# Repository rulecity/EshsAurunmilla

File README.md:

# Esh's Aurunmilla
(Mostly) 1:1 clone of the arcade game PCB for the Funai game, Esh's Aurunmilla

# Introduction
Esh's Aurunmilla was laserdisc game conversion for the 1983 Funai game Interstellar.  It is notoriously campy/cheesy with pretty bad voice acting.  In short, the game is so bad that it's good.

I became fascinated with this game some years ago and desired to own one.  Unfortunately, the PCB and laserdisc are both exceedingly rare.  So instead of finding originals of these items, I created reproductions.  I created a mostly 1:1 clone of the game PCB which is what this repository consists of.  After selling 20 of these clones to collectors and exhausting commercial demand, I decided to open source the whole thing for preservation.  What you have in this repository are the results of my efforts.

# PCBs
I created the PCB with Kicad v5.  I have tested these files on Kicad v6 and they seem to work fine.
I made two smaller PCBs to replace the original PROMs used on these games, which are very obsolete.  The small PCBs use CPLDs to mimic the behavior of the PROMs.  Unfortunately, these CPLDs have themselves become obsolete (I chose them because they were 5V tolerant on the inputs).  But someone who knows what they are doing should be able to update these with a new CPLD/FPGA if they want to badly enough.

I said before that the PCB is a mostly 1:1 clone.  I did change the laserdisc I/O port because the one on the original PCB was hopelessly non-standard.  I also removed some diagnostic stuff that was near the CPU on the original PCB as I saw no benefit to retaining it.  Otherwise, this clone should be nearly identical to the original, trace for trace.

# VHDL
I've included the simple VHDL source code programs I wrote for the two CPLDs.  I built with Xilinx ISE 14.7 which, last I checked, can be obtained for free as a linux VM that runs fine under Windows in VirtualBox.

# Bill of Materials
These are the actual spreadsheets I used when ordering parts for these PCBs.

# Test ROM
A test ROM I wrote from scratch to test PCBs before I shipped them off to customers.  Should be pretty comprehensive.

# More info
See http://www.rulecity.com/esh/

# Support
If you need help building the VHDL code, programming the CPLDs, or having PCBs made from the KiCad files, I offer commercial support: https://www.daphne-emu.com:9443/mediawiki/index.php/CommercialSupport

--Matt Ownby

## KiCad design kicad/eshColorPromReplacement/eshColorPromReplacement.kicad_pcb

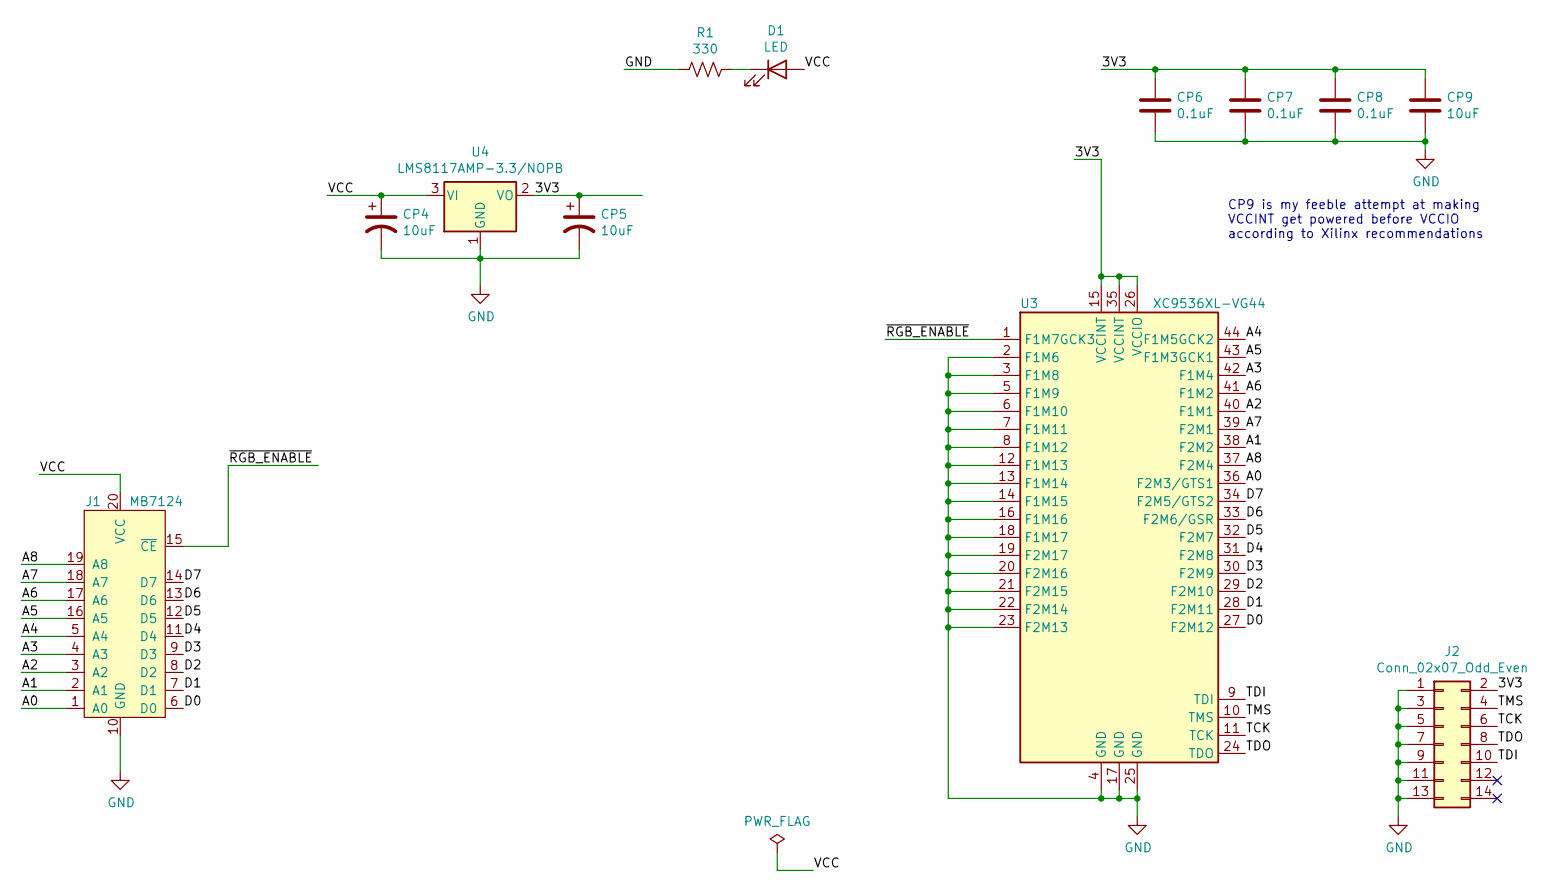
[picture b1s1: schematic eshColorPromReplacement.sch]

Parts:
CP4, CP5, CP9: 10uF; C_1206_3216Metric
CP6, CP7, CP8: 0.1uF; C_1206_3216Metric
D1: LED; LED_1206_3216Metric
J1: MB7124; DIP-20_W7.62mm_Socket
J2: Conn_02x07_Odd_Even; PinHeader_2x07_P2.54mm_Vertical
R1: 330; R_1206_3216Metric
U3: XC9536XL-VG44; TQFP-44_10x10mm_P0.8mm
U4: LMS8117AMP-3.3/NOPB; SOT-223-3_TabPin2

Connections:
/3V3: CP5.1, CP6.1, CP7.1, CP8.1, CP9.1, J2.2, U3.15 (VCCINT), U3.26 (VCCIO), U3.35 (VCCINT), U4.2 (VO)
/A0: J1.1 (A0), U3.36 (F2M3/GTS1)
/A1: J1.2 (A1), U3.38 (F2M2)
/A2: J1.3 (A2), U3.40 (F1M1)
/A3: J1.4 (A3), U3.42 (F1M4)
/A4: J1.5 (A4), U3.44 (F1M5GCK2)
/A5: J1.16 (A5), U3.43 (F1M3GCK1)
/A6: J1.17 (A6), U3.41 (F1M2)
/A7: J1.18 (A7), U3.39 (F2M1)
/A8: J1.19 (A8), U3.37 (F2M4)
/D0: J1.6 (D0), U3.27 (F2M12)
/D1: J1.7 (D1), U3.28 (F2M11)
/D2: J1.8 (D2), U3.29 (F2M10)
/D3: J1.9 (D3), U3.30 (F2M9)
/D4: J1.11 (D4), U3.31 (F2M8)
/D5: J1.12 (D5), U3.32 (F2M7)
/D6: J1.13 (D6), U3.33 (F2M6/GSR)
/D7: J1.14 (D7), U3.34 (F2M5/GTS2)
/TCK: J2.6, U3.11 (TCK)
/TDI: J2.10, U3.9 (TDI)
/TDO: J2.8, U3.24 (TDO)
/TMS: J2.4, U3.10 (TMS)
/VCC: CP4.1, D1.2 (A), J1.20 (VCC), U4.3 (VI)
/~RGB_ENABLE: J1.15 (~CE), U3.1 (F1M7GCK3)
GND: CP4.2, CP5.2, CP6.2, CP7.2, CP8.2, CP9.2, J1.10 (GND), J2.1, J2.3, J2.5, J2.7, J2.9, J2.11, J2.13, R1.2, U3.2 (F1M6), U3.3 (F1M8), U3.4 (GND), U3.5 (F1M9), U3.6 (F1M10), U3.7 (F1M11), U3.8 (F1M12), U3.12 (F1M13), U3.13 (F1M14), U3.14 (F1M15), U3.16 (F1M16), U3.17 (GND), U3.18 (F1M17), U3.19 (F2M17), U3.20 (F2M16), U3.21 (F2M15), U3.22 (F2M14), U3.23 (F2M13), U3.25 (GND), U4.1 (GND)
unnamed: D1.1 (K), R1.1

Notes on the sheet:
CP9 is my feeble attempt at making VCCINT get powered before VCCIO according to Xilinx recommendations

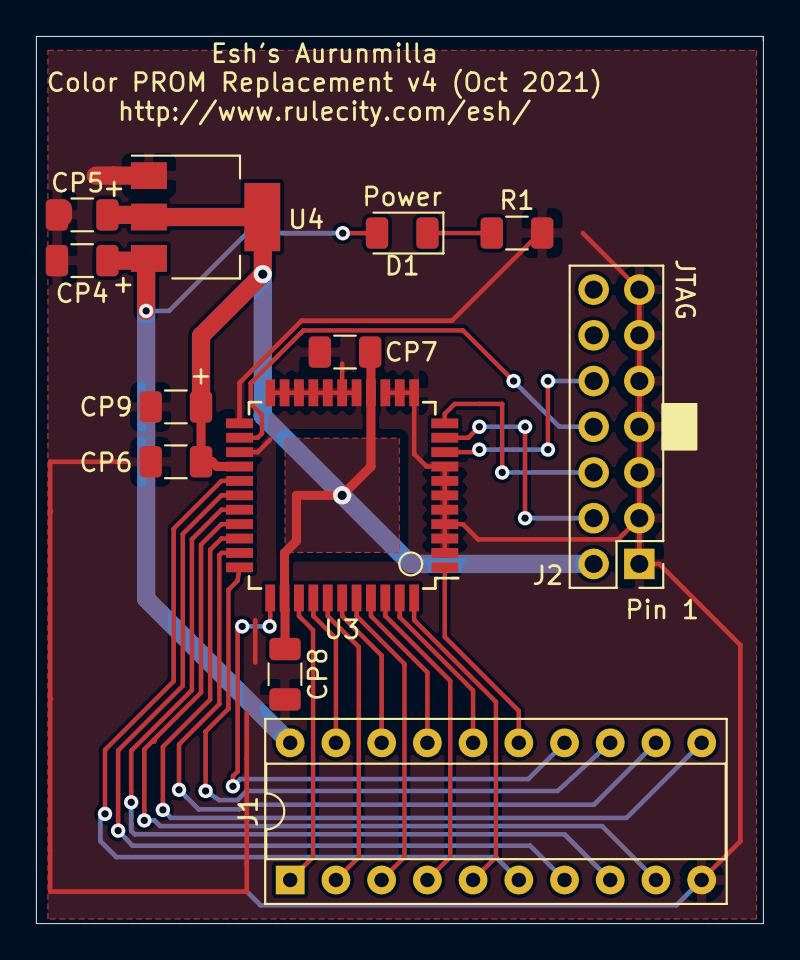
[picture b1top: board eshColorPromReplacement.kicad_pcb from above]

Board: 2 copper layers, 40.4 x 49.3 mm, 12 parts (0 on the bottom side), 26 nets.

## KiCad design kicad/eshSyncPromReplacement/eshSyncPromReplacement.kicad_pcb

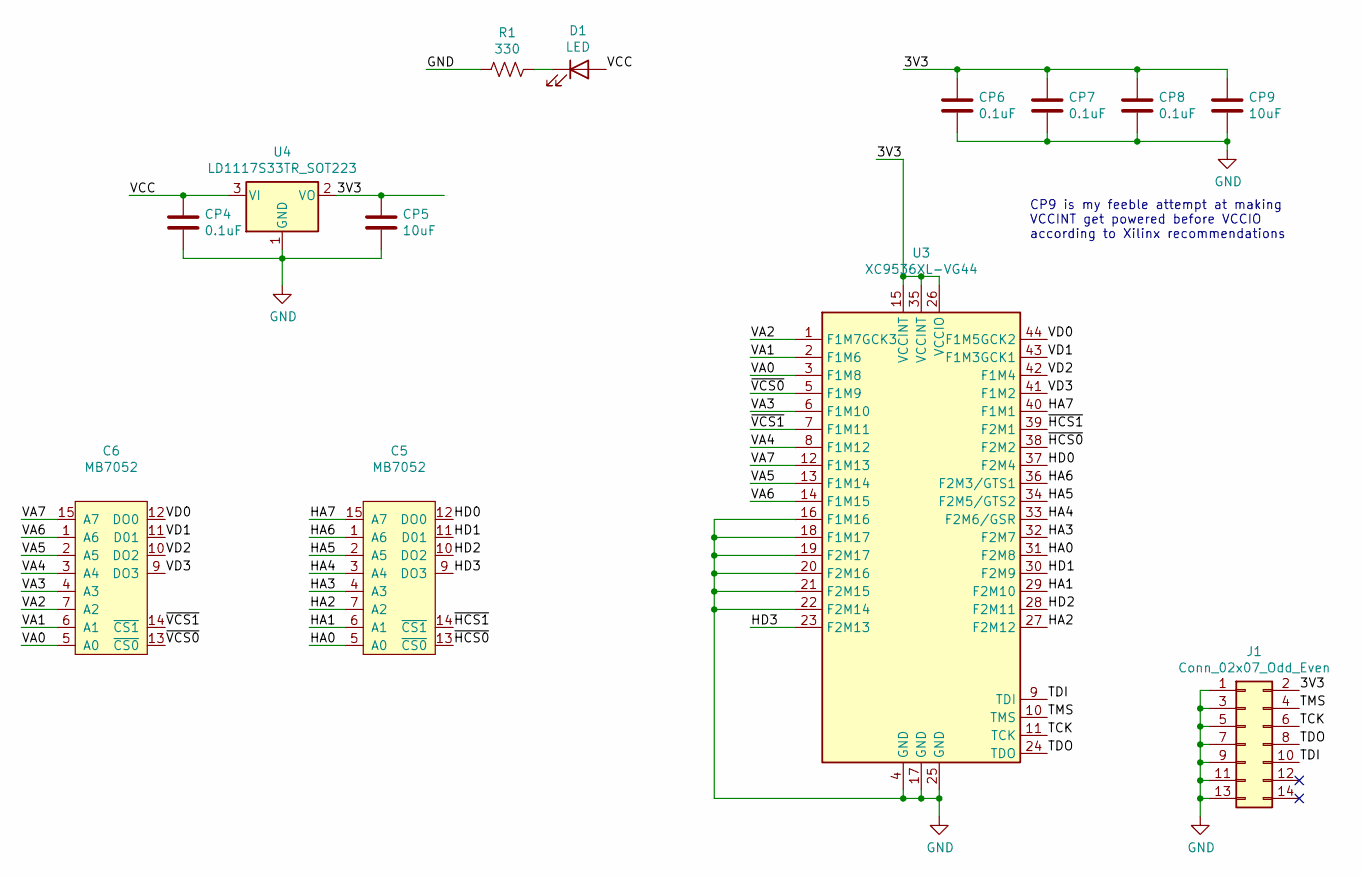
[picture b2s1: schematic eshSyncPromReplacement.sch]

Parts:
C5, C6: MB7052; DIP-16_W7.62mm_Socket
CP4, CP6, CP7, CP8: 0.1uF; C_0603_1608Metric
CP5, CP9: 10uF; C_0603_1608Metric
D1: LED; LED_1206_3216Metric
J1: Conn_02x07_Odd_Even; PinHeader_2x07_P2.54mm_Vertical
R1: 330; R_0603_1608Metric
U3: XC9536XL-VG44; TQFP-44_10x10mm_P0.8mm
U4: LD1117S33TR_SOT223; SOT-223-3_TabPin2

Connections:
/3V3: CP5.1, CP6.1, CP7.1, CP8.1, CP9.1, J1.2, U3.15 (VCCINT), U3.26 (VCCIO), U3.35 (VCCINT), U4.2 (VO)
/HA0: C5.5 (A0), U3.31 (F2M8)
/HA1: C5.6 (A1), U3.29 (F2M10)
/HA2: C5.7 (A2), U3.27 (F2M12)
/HA3: C5.4 (A3), U3.32 (F2M7)
/HA4: C5.3 (A4), U3.33 (F2M6/GSR)
/HA5: C5.2 (A5), U3.34 (F2M5/GTS2)
/HA6: C5.1 (A6), U3.36 (F2M3/GTS1)
/HA7: C5.15 (A7), U3.40 (F1M1)
/HD0: C5.12 (DO0), U3.37 (F2M4)
/HD1: C5.11 (D01), U3.30 (F2M9)
/HD2: C5.10 (DO2), U3.28 (F2M11)
/HD3: C5.9 (DO3), U3.23 (F2M13)
/TCK: J1.6, U3.11 (TCK)
/TDI: J1.10, U3.9 (TDI)
/TDO: J1.8, U3.24 (TDO)
/TMS: J1.4, U3.10 (TMS)
/VA0: C6.5 (A0), U3.3 (F1M8)
/VA1: C6.6 (A1), U3.2 (F1M6)
/VA2: C6.7 (A2), U3.1 (F1M7GCK3)
/VA3: C6.4 (A3), U3.6 (F1M10)
/VA4: C6.3 (A4), U3.8 (F1M12)
/VA5: C6.2 (A5), U3.13 (F1M14)
/VA6: C6.1 (A6), U3.14 (F1M15)
/VA7: C6.15 (A7), U3.12 (F1M13)
/VD0: C6.12 (DO0), U3.44 (F1M5GCK2)
/VD1: C6.11 (D01), U3.43 (F1M3GCK1)
/VD2: C6.10 (DO2), U3.42 (F1M4)
/VD3: C6.9 (DO3), U3.41 (F1M2)
/~HCS0: C5.13 (~CS0), U3.38 (F2M2)
/~HCS1: C5.14 (~CS1), U3.39 (F2M1)
/~VCS0: C6.13 (~CS0), U3.5 (F1M9)
/~VCS1: C6.14 (~CS1), U3.7 (F1M11)
GND: C5.8 (GND), C6.8 (GND), CP4.2, CP5.2, CP6.2, CP7.2, CP8.2, CP9.2, J1.1, J1.3, J1.5, J1.7, J1.9, J1.11, J1.13, R1.2, U3.4 (GND), U3.16 (F1M16), U3.17 (GND), U3.18 (F1M17), U3.19 (F2M17), U3.20 (F2M16), U3.21 (F2M15), U3.22 (F2M14), U3.25 (GND), U4.1 (GND)
unnamed: D1.1 (K), R1.1
VCC: C5.16 (VCC), C6.16 (VCC), CP4.1, D1.2 (A), U4.3 (VI)

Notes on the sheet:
CP9 is my feeble attempt at making VCCINT get powered before VCCIO according to Xilinx recommendations

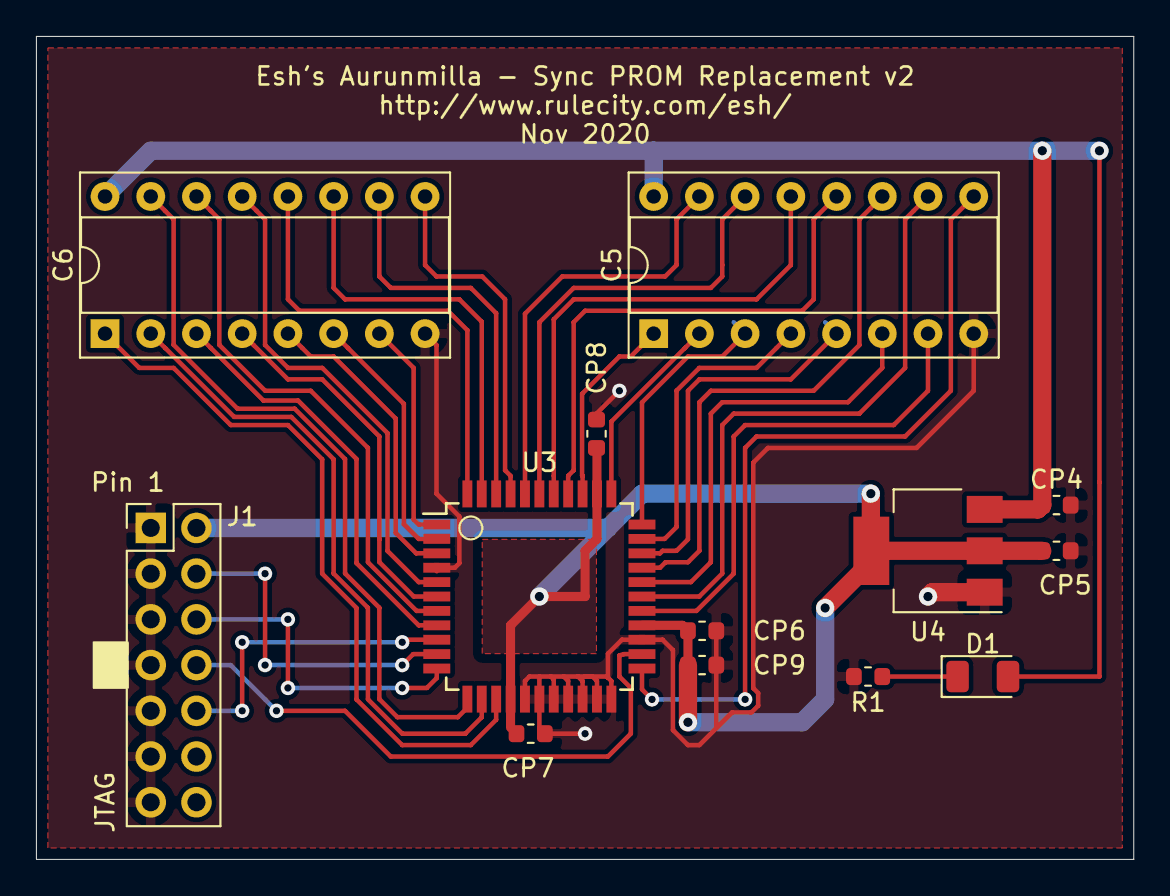
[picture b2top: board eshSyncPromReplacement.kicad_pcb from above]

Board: 2 copper layers, 61.0 x 45.7 mm, 13 parts (0 on the bottom side), 36 nets.

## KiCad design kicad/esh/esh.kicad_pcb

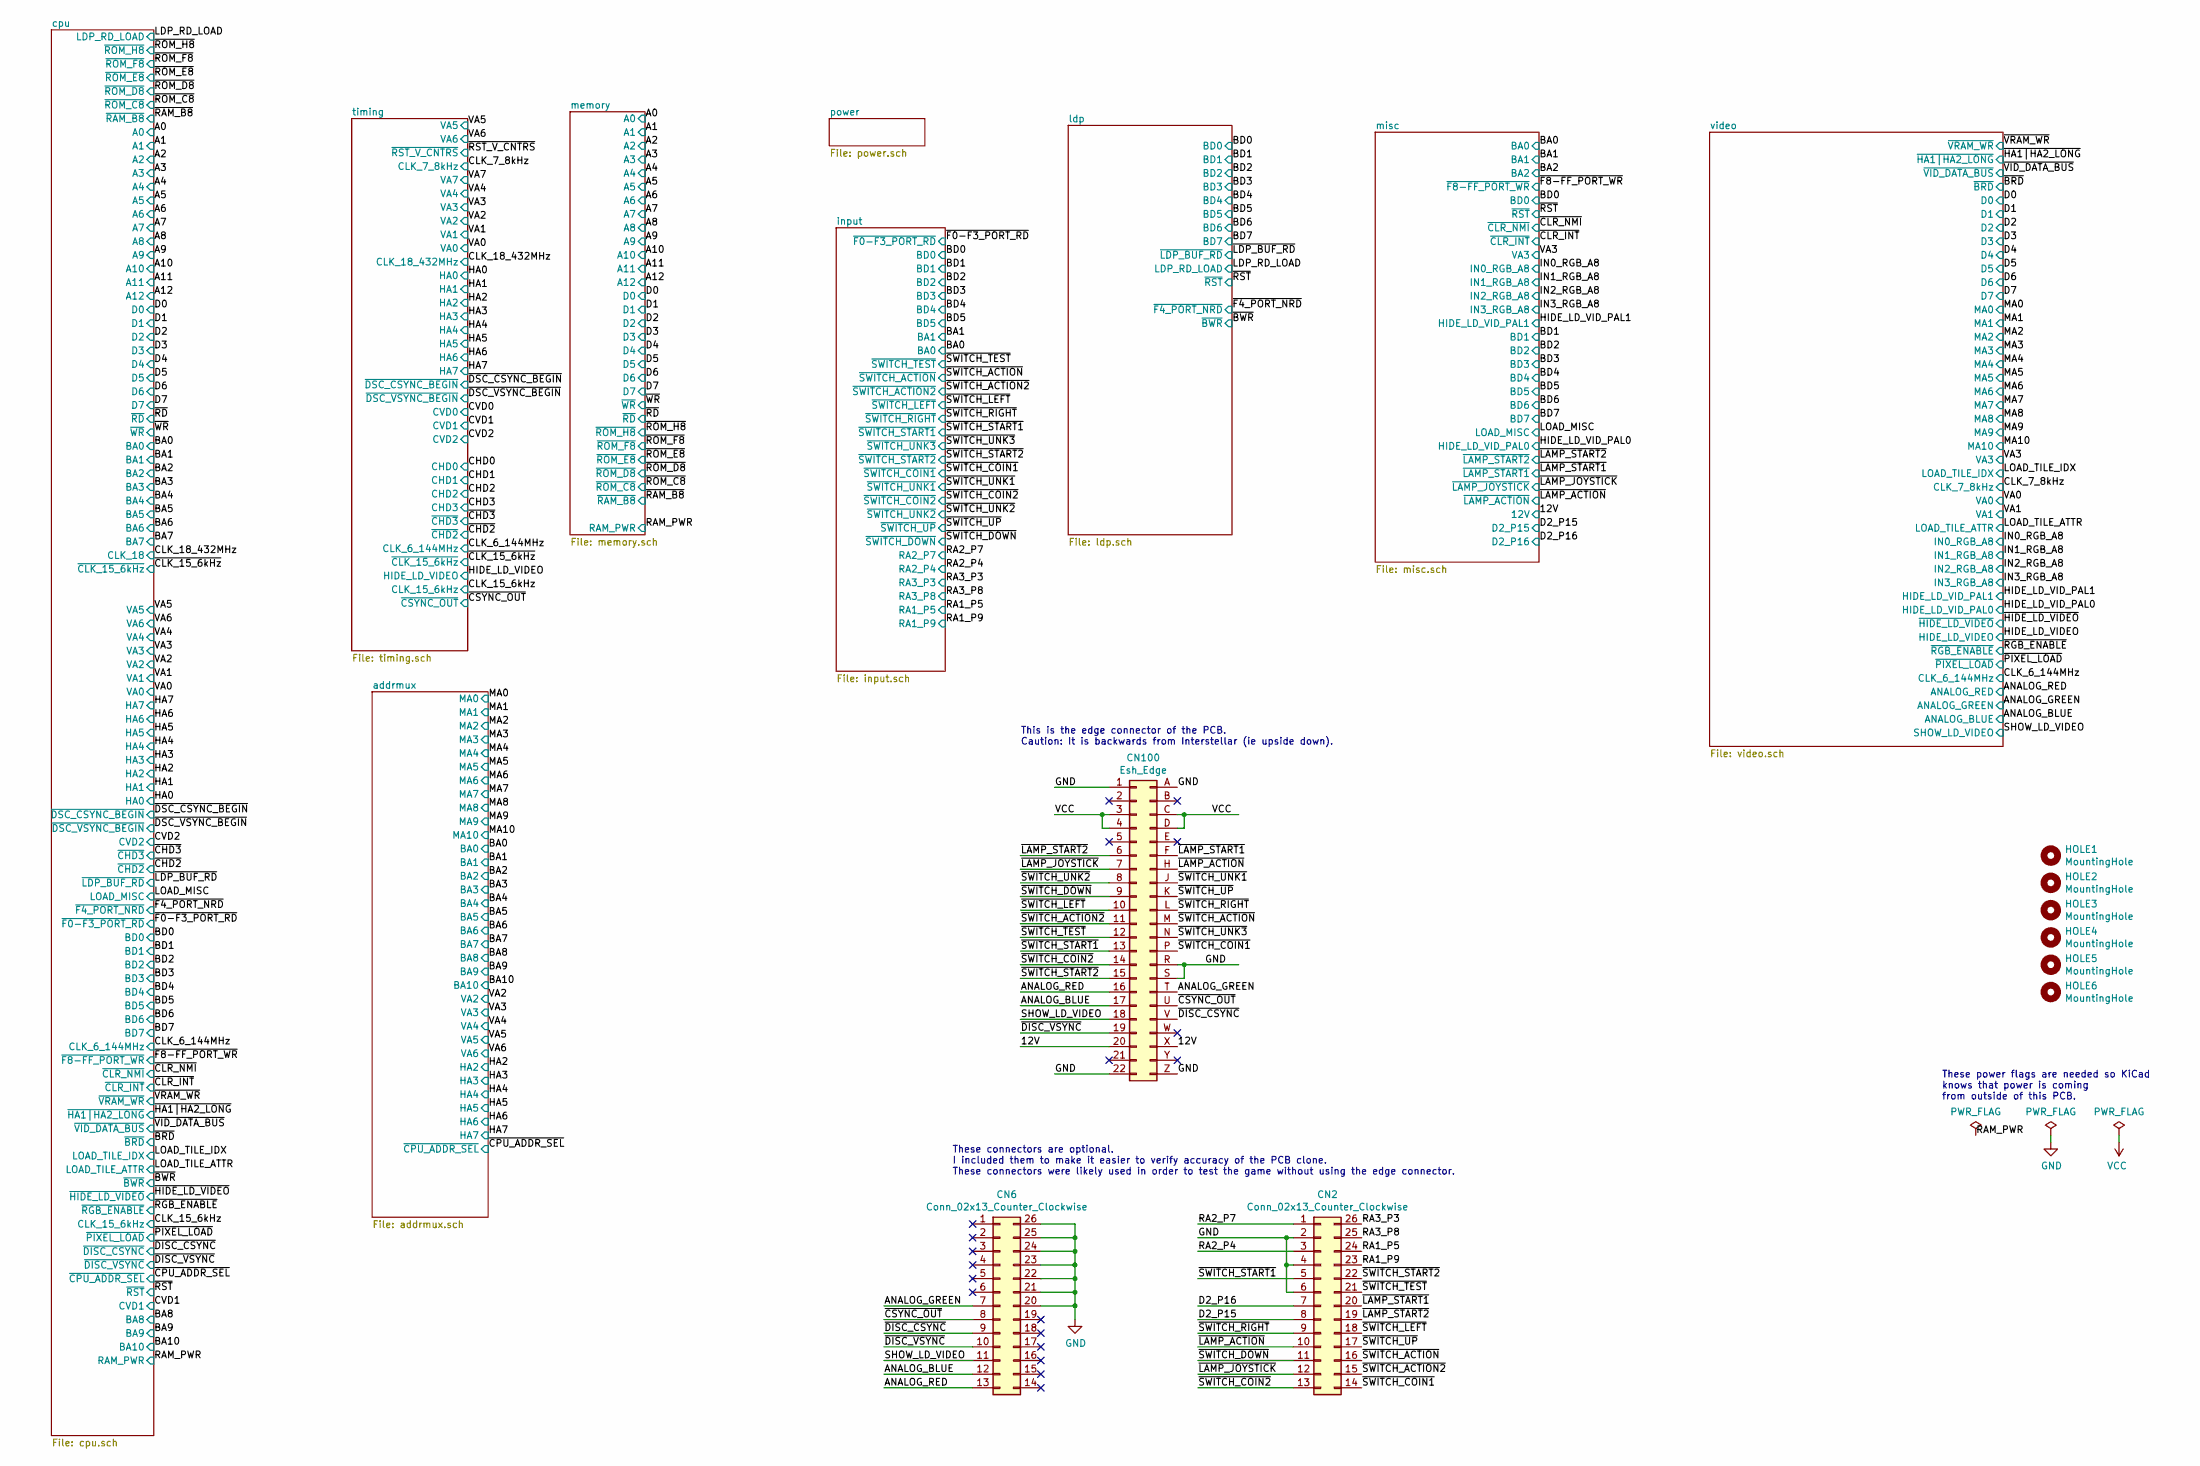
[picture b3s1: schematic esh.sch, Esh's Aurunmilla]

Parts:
CN2, CN6: Conn_02x13_Counter_Clockwise; 2x13Connector
CN100: Esh_Edge
HOLE1, HOLE2, HOLE3, HOLE4, HOLE5, HOLE6: MountingHole; MountingHole_4mm

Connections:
/12V: CN100.20, CN100.X; also elsewhere on the board
/ANALOG_BLUE: CN6.12, CN100.17; also elsewhere on the board
/ANALOG_GREEN: CN6.7, CN100.T; also elsewhere on the board
/ANALOG_RED: CN6.13, CN100.16; also elsewhere on the board
/D2_P15: CN2.8; also elsewhere on the board
/D2_P16: CN2.7; also elsewhere on the board
/RA1_P5: CN2.24; also elsewhere on the board
/RA1_P9: CN2.23; also elsewhere on the board
/RA2_P4: CN2.3; also elsewhere on the board
/RA2_P7: CN2.1; also elsewhere on the board
/RA3_P3: CN2.26; also elsewhere on the board
/RA3_P8: CN2.25; also elsewhere on the board
/SHOW_LD_VIDEO: CN6.11, CN100.18; also elsewhere on the board
/~CSYNC_OUT: CN6.8, CN100.U; also elsewhere on the board
/~DISC_CSYNC: CN6.9, CN100.V; also elsewhere on the board
/~DISC_VSYNC: CN6.10, CN100.19; also elsewhere on the board
/~LAMP_ACTION: CN2.10, CN100.H; also elsewhere on the board
/~LAMP_JOYSTICK: CN2.12, CN100.7; also elsewhere on the board
/~LAMP_START1: CN2.20, CN100.F; also elsewhere on the board
/~LAMP_START2: CN2.19, CN100.6; also elsewhere on the board
/~SWITCH_ACTION: CN2.16, CN100.M; also elsewhere on the board
/~SWITCH_ACTION2: CN2.15, CN100.11; also elsewhere on the board
/~SWITCH_COIN1: CN2.14, CN100.P; also elsewhere on the board
/~SWITCH_COIN2: CN2.13, CN100.14; also elsewhere on the board
/~SWITCH_DOWN: CN2.11, CN100.9; also elsewhere on the board
/~SWITCH_LEFT: CN2.18, CN100.10; also elsewhere on the board
/~SWITCH_RIGHT: CN2.9, CN100.L; also elsewhere on the board
/~SWITCH_START1: CN2.5, CN100.13; also elsewhere on the board
/~SWITCH_START2: CN2.22, CN100.15; also elsewhere on the board
/~SWITCH_TEST: CN2.21, CN100.12; also elsewhere on the board
/~SWITCH_UNK1: CN100.J; also elsewhere on the board
/~SWITCH_UNK2: CN100.8; also elsewhere on the board
/~SWITCH_UNK3: CN100.N; also elsewhere on the board
/~SWITCH_UP: CN2.17, CN100.K; also elsewhere on the board
GND: CN2.2, CN2.4, CN2.6, CN6.20, CN6.21, CN6.22, CN6.23, CN6.24, CN6.25, CN6.26, CN100.1, CN100.22, CN100.A, CN100.R, CN100.S, CN100.Z; also elsewhere on the board
VCC: CN100.3, CN100.4, CN100.C, CN100.D; also elsewhere on the board

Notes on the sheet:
These power flags are needed so KiCad knows that power is coming from outside of this PCB.
These connectors are optional. I included them to make it easier to verify accuracy of the PCB clone. These connectors were likely used in order to test the game without using the edge connector.
This is the edge connector of the PCB. Caution: It is backwards from Interstellar (ie upside down).

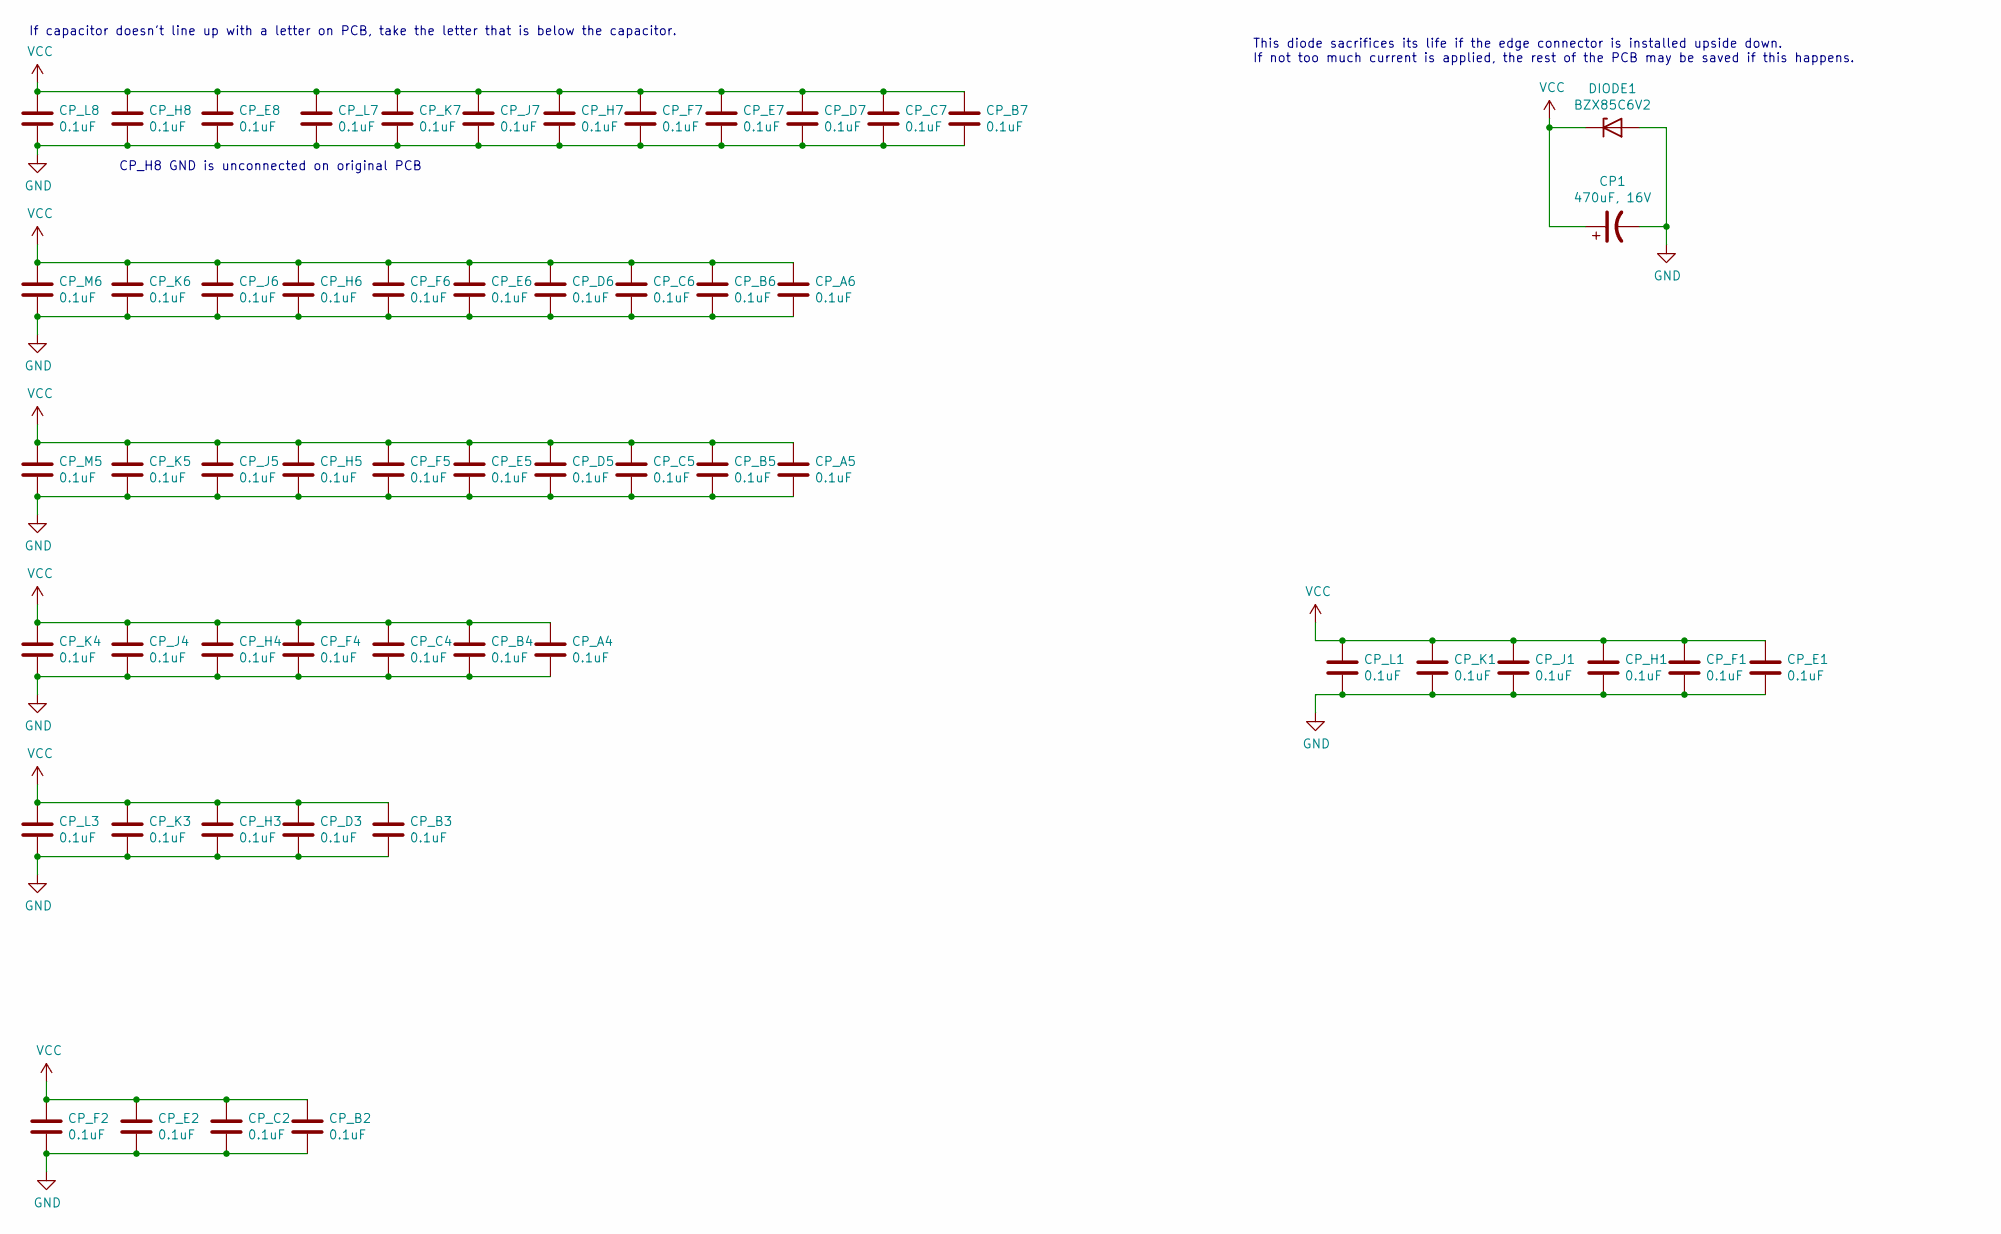
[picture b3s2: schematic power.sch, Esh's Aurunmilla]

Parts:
CP1: 470uF, 16V; CP_Radial_D8.0mm_P5.00mm
CP_A4, CP_A5, CP_A6: 0.1uF; R_Axial_DIN0204_L3.6mm_D1.6mm_P5.08mm_Horizontal
CP_B2, CP_B3, CP_B4, CP_B5, CP_B6, CP_B7: 0.1uF; R_Axial_DIN0204_L3.6mm_D1.6mm_P5.08mm_Horizontal
CP_C2, CP_C4, CP_C5, CP_C6, CP_C7: 0.1uF; R_Axial_DIN0204_L3.6mm_D1.6mm_P5.08mm_Horizontal
CP_D3, CP_D5, CP_D6, CP_D7: 0.1uF; R_Axial_DIN0204_L3.6mm_D1.6mm_P5.08mm_Horizontal
CP_E1, CP_E2, CP_E5, CP_E6, CP_E7, CP_E8: 0.1uF; R_Axial_DIN0204_L3.6mm_D1.6mm_P5.08mm_Horizontal
CP_F1, CP_F2, CP_F4, CP_F5, CP_F6, CP_F7: 0.1uF; R_Axial_DIN0204_L3.6mm_D1.6mm_P5.08mm_Horizontal
CP_H1, CP_H3, CP_H4, CP_H5, CP_H6, CP_H7, CP_H8: 0.1uF; R_Axial_DIN0204_L3.6mm_D1.6mm_P5.08mm_Horizontal
CP_J1, CP_J4, CP_J5, CP_J6, CP_J7: 0.1uF; R_Axial_DIN0204_L3.6mm_D1.6mm_P5.08mm_Horizontal
CP_K1, CP_K3, CP_K4, CP_K5, CP_K6, CP_K7: 0.1uF; R_Axial_DIN0204_L3.6mm_D1.6mm_P5.08mm_Horizontal
CP_L1, CP_L3, CP_L7, CP_L8: 0.1uF; R_Axial_DIN0204_L3.6mm_D1.6mm_P5.08mm_Horizontal
CP_M5, CP_M6: 0.1uF; R_Axial_DIN0204_L3.6mm_D1.6mm_P5.08mm_Horizontal
DIODE1: BZX85C6V2; D_T-1_P10.16mm_Horizontal

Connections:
GND: CP1.2, CP_A4.2, CP_A5.2, CP_A6.2, CP_B2.2, CP_B3.2, CP_B4.2, CP_B5.2, CP_B6.2, CP_B7.2, CP_C2.2, CP_C4.2, CP_C5.2, CP_C6.2, CP_C7.2, CP_D3.2, CP_D5.2, CP_D6.2, CP_D7.2, CP_E1.2, CP_E2.2, CP_E5.2, CP_E6.2, CP_E7.2, CP_E8.2, CP_F1.2, CP_F2.2, CP_F4.2, CP_F5.2, CP_F6.2, CP_F7.2, CP_H1.2, CP_H3.2, CP_H4.2, CP_H5.2, CP_H6.2, CP_H7.2, CP_H8.2, CP_J1.2, CP_J4.2, CP_J5.2, CP_J6.2, CP_J7.2, CP_K1.2, CP_K3.2, CP_K4.2, CP_K5.2, CP_K6.2, CP_K7.2, CP_L1.2, CP_L3.2, CP_L7.2, CP_L8.2, CP_M5.2, CP_M6.2, DIODE1.2 (A); also elsewhere on the board
VCC: CP1.1, CP_A4.1, CP_A5.1, CP_A6.1, CP_B2.1, CP_B3.1, CP_B4.1, CP_B5.1, CP_B6.1, CP_B7.1, CP_C2.1, CP_C4.1, CP_C5.1, CP_C6.1, CP_C7.1, CP_D3.1, CP_D5.1, CP_D6.1, CP_D7.1, CP_E1.1, CP_E2.1, CP_E5.1, CP_E6.1, CP_E7.1, CP_E8.1, CP_F1.1, CP_F2.1, CP_F4.1, CP_F5.1, CP_F6.1, CP_F7.1, CP_H1.1, CP_H3.1, CP_H4.1, CP_H5.1, CP_H6.1, CP_H7.1, CP_H8.1, CP_J1.1, CP_J4.1, CP_J5.1, CP_J6.1, CP_J7.1, CP_K1.1, CP_K3.1, CP_K4.1, CP_K5.1, CP_K6.1, CP_K7.1, CP_L1.1, CP_L3.1, CP_L7.1, CP_L8.1, CP_M5.1, CP_M6.1, DIODE1.1 (K); also elsewhere on the board

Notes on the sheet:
If capacitor doesn't line up with a letter on PCB, take the letter that is below the capacitor.
CP_H8 GND is unconnected on original PCB
This diode sacrifices its life if the edge connector is installed upside down. If not too much current is applied, the rest of the PCB may be saved if this happens.

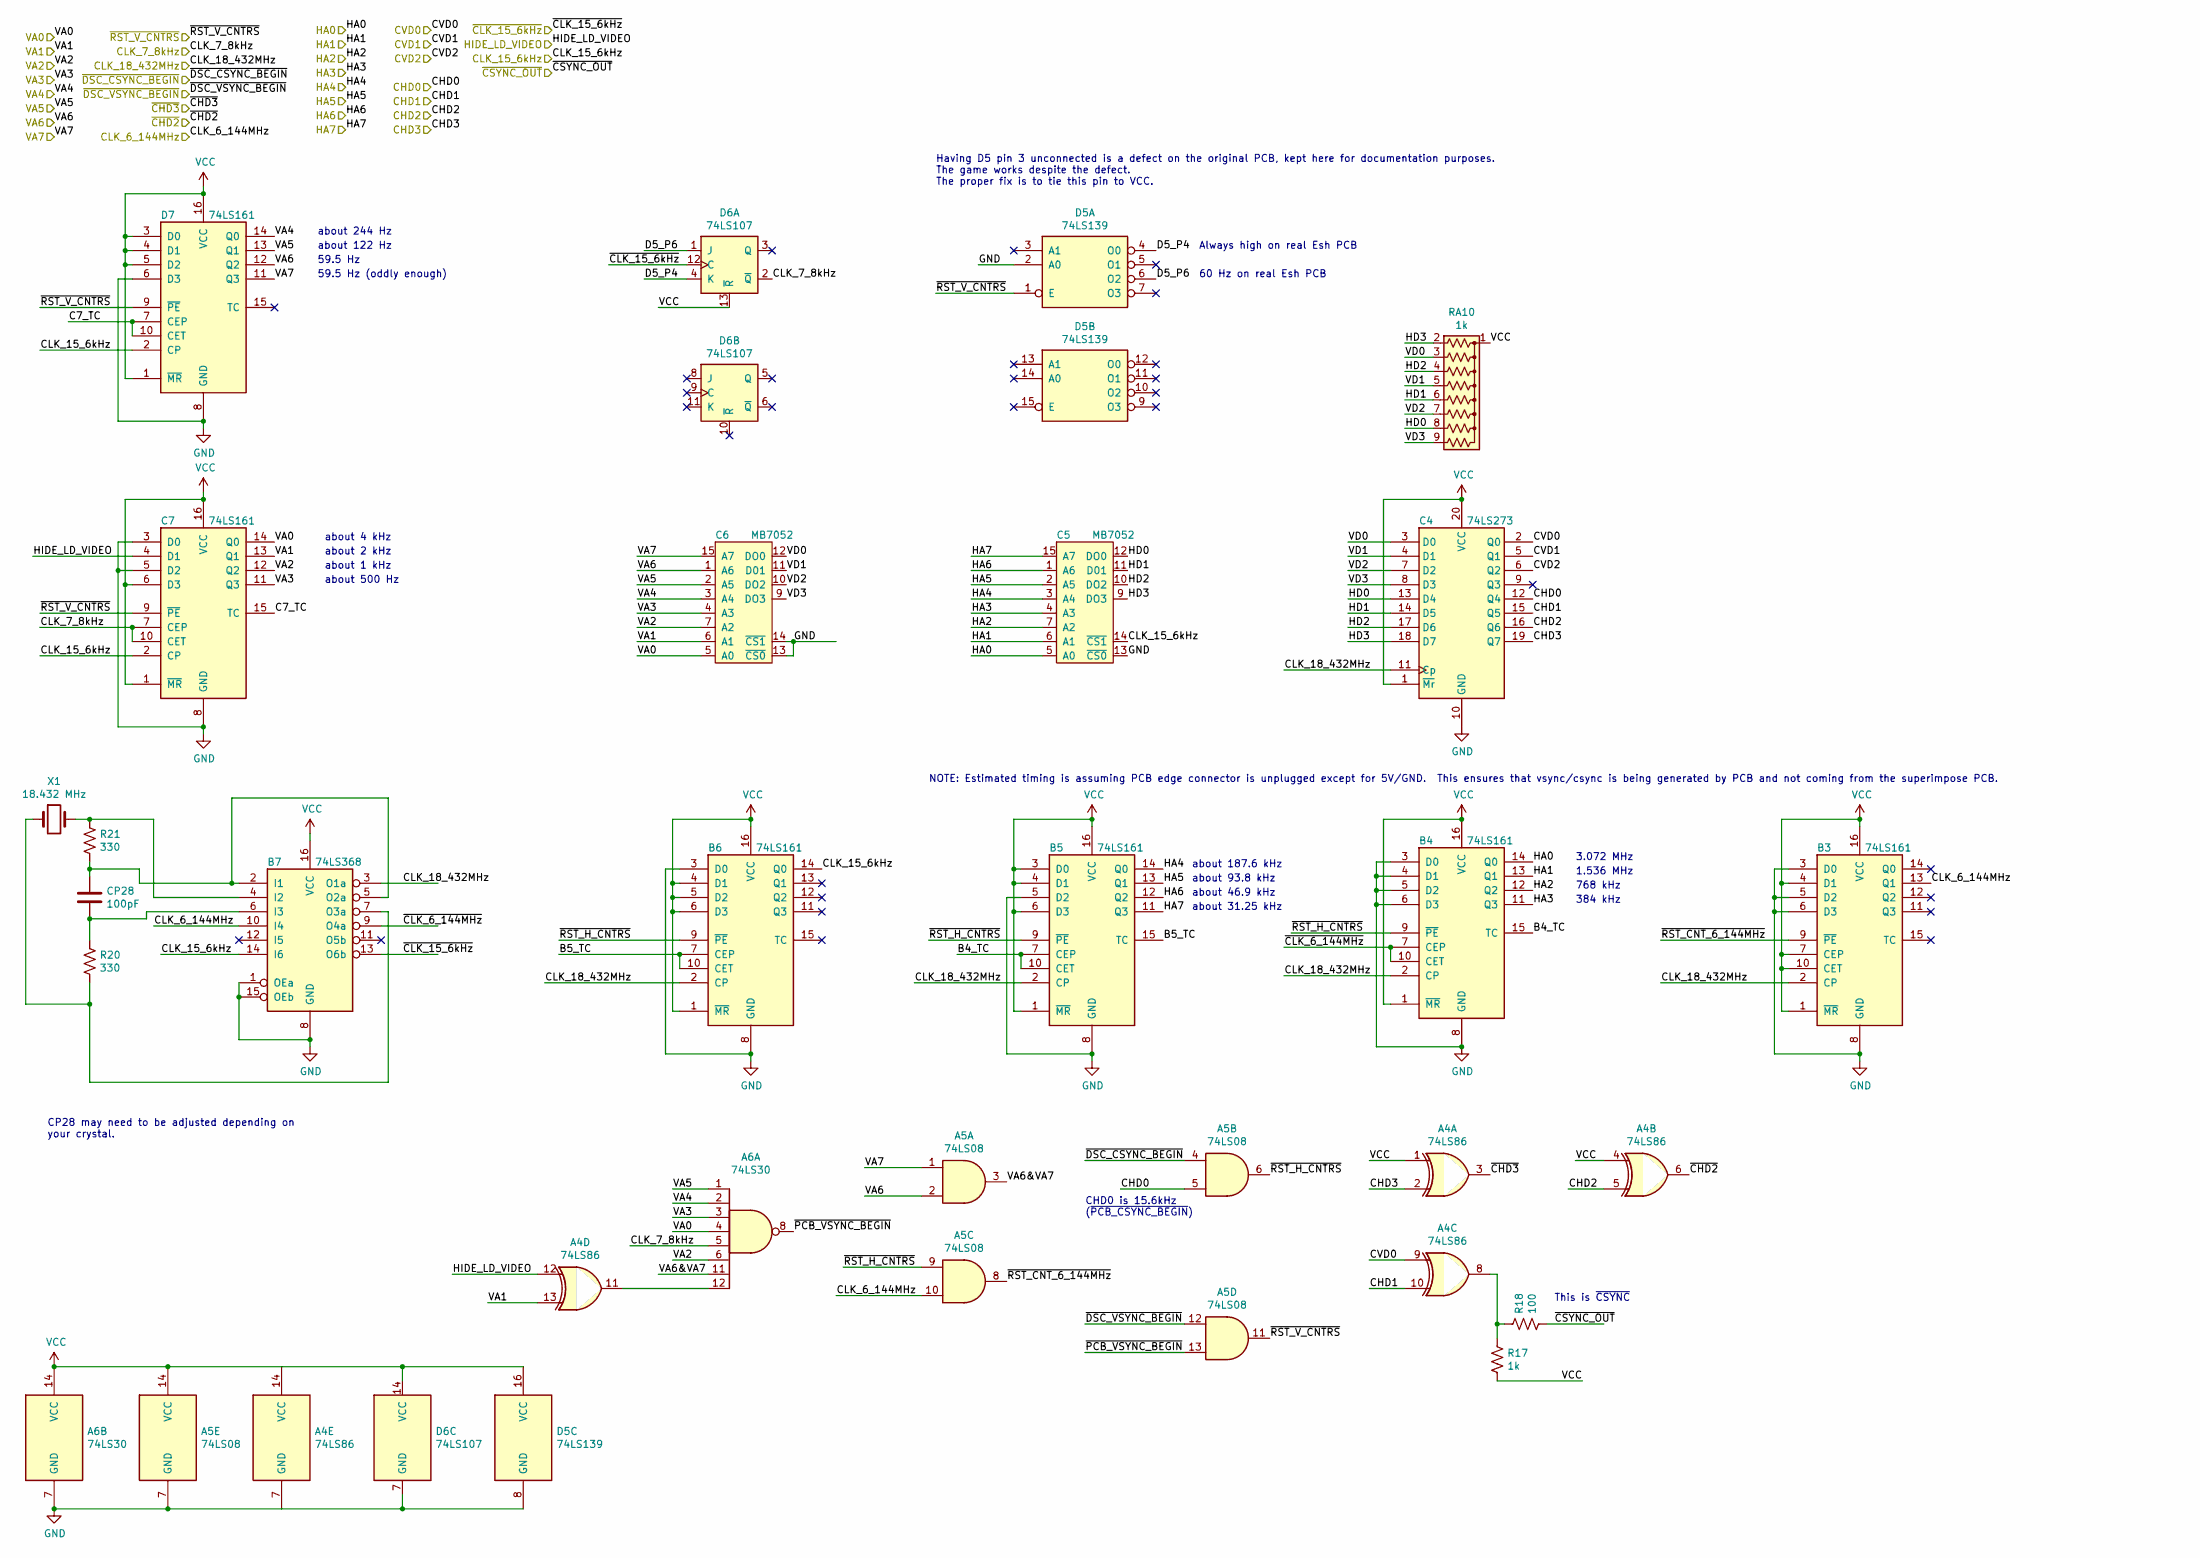
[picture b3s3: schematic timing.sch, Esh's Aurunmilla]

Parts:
A4: 74LS86; DIP-14_W7.62mm_Socket
A5: 74LS08; DIP-14_W7.62mm_Socket
A6: 74LS30; DIP-14_W7.62mm_Socket
B3, B4, B5, B6: 74LS161; DIP-16_W7.62mm_Socket
B7: 74LS368; DIP-16_W7.62mm_Socket
C4: 74LS273; DIP-20_W7.62mm_Socket
C5, C6: MB7052; DIP-16_W7.62mm_Socket
C7: 74LS161; DIP-16_W7.62mm_Socket
CP28: 100pF; R_Axial_DIN0204_L3.6mm_D1.6mm_P5.08mm_Horizontal
D5: 74LS139; DIP-16_W7.62mm_Socket
D6: 74LS107; DIP-14_W7.62mm_Socket
D7: 74LS161; DIP-16_W7.62mm_Socket
R17: 1k; R_Axial_DIN0207_L6.3mm_D2.5mm_P10.16mm_Horizontal
R18: 100; R_Axial_DIN0207_L6.3mm_D2.5mm_P10.16mm_Horizontal
R20, R21: 330; R_Axial_DIN0207_L6.3mm_D2.5mm_P10.16mm_Horizontal
RA10: 1k; R_Array_SIP9
X1: 18.432 MHz; Crystal_HC49-U_Vertical

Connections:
/CHD0: A5.5, C4.12 (Q4)
/CHD1: A4.10, C4.15 (Q5)
/CHD2: A4.5, C4.16 (Q6)
/CHD3: A4.2, C4.19 (Q7)
/CLK_6_144MHz: A5.10, B3.13 (Q1), B7.10 (I4); also elsewhere on the board
/CLK_7_8kHz: A6.5, C7.7 (CEP), C7.10 (CET), D6.2 (~Q); also elsewhere on the board
/CLK_15_6kHz: B6.14 (Q0), B7.14 (I6), C5.14 (~CS1), C7.2 (CP), D7.2 (CP); also elsewhere on the board
/CLK_18_432MHz: B3.2 (CP), B4.2 (CP), B5.2 (CP), B6.2 (CP), B7.3 (O1a), C4.11 (Cp); also elsewhere on the board
/CVD0: A4.9, C4.2 (Q0)
/CVD1: C4.5 (Q1); also elsewhere on the board
/CVD2: C4.6 (Q2); also elsewhere on the board
/HA0: B4.14 (Q0), C5.5 (A0); also elsewhere on the board
/HA1: B4.13 (Q1), C5.6 (A1); also elsewhere on the board
/HA2: B4.12 (Q2), C5.7 (A2); also elsewhere on the board
/HA3: B4.11 (Q3), C5.4 (A3); also elsewhere on the board
/HA4: B5.14 (Q0), C5.3 (A4); also elsewhere on the board
/HA5: B5.13 (Q1), C5.2 (A5); also elsewhere on the board
/HA6: B5.12 (Q2), C5.1 (A6); also elsewhere on the board
/HA7: B5.11 (Q3), C5.15 (A7); also elsewhere on the board
/HIDE_LD_VIDEO: A4.12, C7.4 (D1); also elsewhere on the board
/VA0: A6.4, C6.5 (A0), C7.14 (Q0); also elsewhere on the board
/VA1: A4.13, C6.6 (A1), C7.13 (Q1); also elsewhere on the board
/VA2: A6.6, C6.7 (A2), C7.12 (Q2); also elsewhere on the board
/VA3: A6.3, C6.4 (A3), C7.11 (Q3); also elsewhere on the board
/VA4: A6.2, C6.3 (A4), D7.14 (Q0); also elsewhere on the board
/VA5: A6.1, C6.2 (A5), D7.13 (Q1); also elsewhere on the board
/VA6: A5.2, C6.1 (A6), D7.12 (Q2); also elsewhere on the board
/VA7: A5.1, C6.15 (A7), D7.11 (Q3)
/timing/B4_TC: B4.15 (TC), B5.7 (CEP), B5.10 (CET)
/timing/B5_TC: B5.15 (TC), B6.7 (CEP), B6.10 (CET)
/timing/C7_TC: C7.15 (TC), D7.7 (CEP), D7.10 (CET)
/timing/D5_P4: D5.4 (O0), D6.4 (K)
/timing/D5_P6: D5.6 (O2), D6.1 (J)
/timing/HD0: C4.13 (D4), C5.12 (DO0), RA10.8 (R7)
/timing/HD1: C4.14 (D5), C5.11 (D01), RA10.6 (R5)
/timing/HD2: C4.17 (D6), C5.10 (DO2), RA10.4 (R3)
/timing/HD3: C4.18 (D7), C5.9 (DO3), RA10.2 (R1)
/timing/VA6&VA7: A5.3, A6.11
/timing/VD0: C4.3 (D0), C6.12 (DO0), RA10.3 (R2)
/timing/VD1: C4.4 (D1), C6.11 (D01), RA10.5 (R4)
/timing/VD2: C4.7 (D2), C6.10 (DO2), RA10.7 (R6)
/timing/VD3: C4.8 (D3), C6.9 (DO3), RA10.9 (R8)
/timing/~CLK_6_144MHz: B4.7 (CEP), B4.10 (CET), B7.9 (O4a)
/timing/~PCB_VSYNC_BEGIN: A5.13, A6.8
/timing/~RST_CNT_6_144MHz: A5.8, B3.9 (~PE)
/timing/~RST_H_CNTRS: A5.6, A5.9, B4.9 (~PE), B5.9 (~PE), B6.9 (~PE)
/~CHD2: A4.6; also elsewhere on the board
/~CHD3: A4.3; also elsewhere on the board
/~CLK_15_6kHz: B7.13 (O6b), D6.12 (C); also elsewhere on the board
/~CSYNC_OUT: R18.1; also elsewhere on the board
/~DSC_CSYNC_BEGIN: A5.4; also elsewhere on the board
/~DSC_VSYNC_BEGIN: A5.12; also elsewhere on the board
/~RST_V_CNTRS: A5.11, C7.9 (~PE), D5.1 (E), D7.9 (~PE)
GND: A4.7 (GND), A5.7 (GND), A6.7 (GND), B3.3 (D0), B3.5 (D2), B3.6 (D3), B3.8 (GND), B4.3 (D0), B4.4 (D1), B4.5 (D2), B4.6 (D3), B4.8 (GND), B5.5 (D2), B5.8 (GND), B6.3 (D0), B6.8 (GND), B7.1 (OEa), B7.8 (GND), B7.15 (OEb), C4.10 (GND), C5.8 (GND), C5.13 (~CS0), C6.8 (GND), C6.13 (~CS0), C6.14 (~CS1), C7.3 (D0), C7.5 (D2), C7.8 (GND), D5.2 (A0), D5.8 (GND), D6.7 (GND), D7.6 (D3), D7.8 (GND); also elsewhere on the board
unnamed: A4.8, R17.2, R18.2
unnamed: A4.11, A6.12
unnamed: B7.2 (I1), B7.5 (O2a), CP28.1, R21.1
unnamed: B7.4 (I2), R21.2, X1.2
unnamed: B7.6 (I3), CP28.2, R20.2
unnamed: B7.7 (O3a), R20.1, X1.1
VCC: A4.1, A4.4, A4.14 (VCC), A5.14 (VCC), A6.14 (VCC), B3.1 (~MR), B3.4 (D1), B3.7 (CEP), B3.10 (CET), B3.16 (VCC), B4.1 (~MR), B4.16 (VCC), B5.1 (~MR), B5.3 (D0), B5.4 (D1), B5.6 (D3), B5.16 (VCC), B6.1 (~MR), B6.4 (D1), B6.5 (D2), B6.6 (D3), B6.16 (VCC), B7.16 (VCC), C4.1 (~Mr), C4.20 (VCC), C5.16 (VCC), C6.16 (VCC), C7.1 (~MR), C7.6 (D3), C7.16 (VCC), D5.16 (VCC), D6.13 (~R), D6.14 (VCC), D7.1 (~MR), D7.3 (D0), D7.4 (D1), D7.5 (D2), D7.16 (VCC), R17.1, RA10.1 (common); also elsewhere on the board

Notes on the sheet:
Always high on real Esh PCB
60 Hz on real Esh PCB
3.072 MHz
1.536 MHz
768 kHz
384 kHz
about 31.25 kHz
about 46.9 kHz
about 93.8 kHz
about 187.6 kHz
about 244 Hz
about 122 Hz
59.5 Hz
59.5 Hz (oddly enough)
about 4 kHz
about 2 kHz
about 1 kHz
about 500 Hz
CHD0 is 15.6kHz (~PCB_CSYNC_BEGIN)
This is ~CSYNC
Having D5 pin 3 unconnected is a defect on the original PCB, kept here for documentation purposes. The game works despite the defect. The proper fix is to tie this pin to VCC.
CP28 may need to be adjusted depending on your crystal.
NOTE: Estimated timing is assuming PCB edge connector is unplugged except for 5V/GND. This ensures that vsync/csync is being generated by PCB and not coming from the superimpose PCB.
